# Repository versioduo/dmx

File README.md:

# dmx
🚥 MIDI to DMX Controller

## Configuration
Up to 16 DMX devices are mapped to 16 MIDI channels. The DMX
devices are configured by their base DMX address and the number
of DMX channels to control.

Default power-on values can be stored in the configuration. A MIDI
_System-Reset_ message will reset all devices and channels to their
configured power-on values.

For RGB devices, it is possible to use a separate set of more
intuitive CC values to control _Brightness_, _Colour_, _Saturation_;
the controller will calculate the RGB channel values accordingly.

## Controllers
MIDI Control Change (CC) values control the DMX channel values.

## Notes
The velocity value of a note overwrites the corresponding CC value
for the duration of the note; a MIDI _Note-Off_ will reset the DMX channel
value to the current CC value. A MIDI _All-Notes-Off_ message will restore
all devices and channels to the currently configured controller values.

During an active note, channel aftertouch will change the _Brightness_,
pitch bend will change the _Colour_.

There are two programs (MIDI _Program Change_) for notes. _Channels_
maps a range of consecutive notes to DMX channels.

_Brightness_ maps all received notes (the pitch is ignored) to control
only the brightness (or the first DMX channel of the device) of the DMX device.
If multiple notes are played at the same time, a MIDI _Note-Off_ will restore
the value of the earlier, still active note.

## Max For Live Device
An optional Ableton Max4Live [device](https://github.com/versioduo/max4live)
allows the the direct mapping from Live Automation to DMX values.

To avoid inconsistencies it will monitor the Live transport state, and update
all configured DMX channels of the current device every time _Play_ or
_Stop_ are triggered.

## Hardware

# Copying
Anyone can use this public domain work without having to seek authorisation, no one can ever own it.

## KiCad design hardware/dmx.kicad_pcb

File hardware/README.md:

# dmx-hardware

🚥 MIDI to DMX Bridge

## Board

## Schematic

[PDF](dmx.pdf)

## Bill Of Materials

[Interactive BOM](https://versioduo.com/view?url=https://raw.githubusercontent.com/versioduo/dmx/refs/heads/main/hardware/dmx-bom.html)

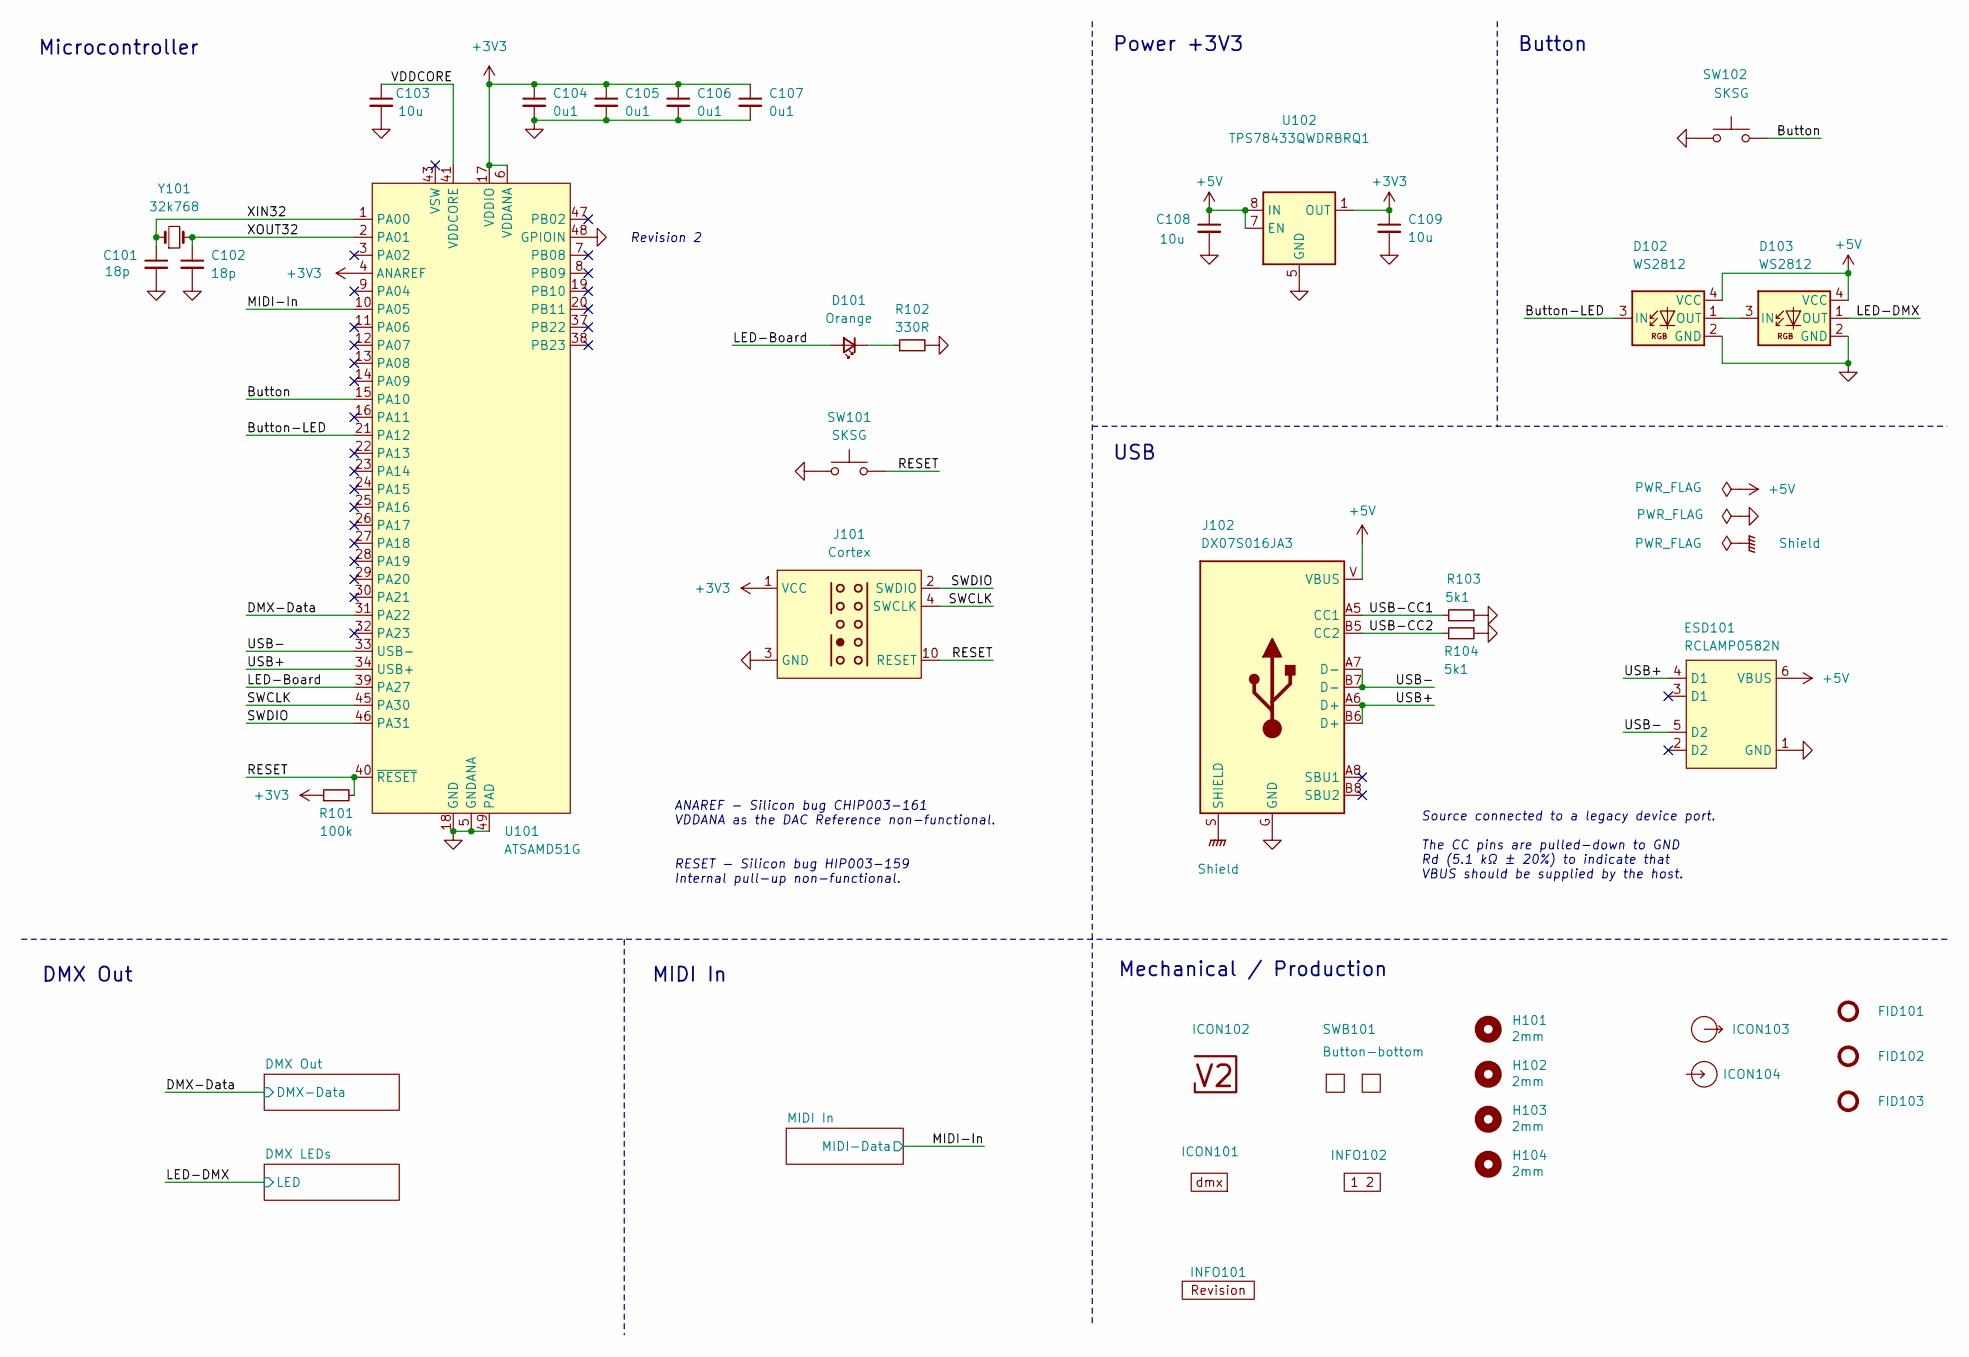
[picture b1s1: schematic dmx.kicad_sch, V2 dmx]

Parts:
C101, C102: 18p; C_1608; Rating 50V; Mouser 810-CGA3E2C0G1H180J
C103: 10u; C_1608; Rating 10V; Mouser 810-C1608X6S1A106M
C104, C105, C106, C107: 0u1; C_1608; Rating 50V; Mouser 810-CGA3E2X7R1H104MA
C108, C109: 10u; C_2012; Rating 25V; Mouser 810-C2012X5R1E106K
D101: Orange; LED_1608; Rating 605nm; Mouser 755-SML-D12D1WT86
D102, D103: WS2812; WS2812-2020; Rating 15mA; LCSC C965555
ESD101: RCLAMP0582N; SLP1210N6; Rating 20kV; Mouser 947-RCLAMP0582N.TCT
FID101, FID102, FID103: Fiducial_Paste; Fiducial_0.5mm_Mask1mm_Paste
H101, H102, H103, H104: 2mm; MountingHole_2mm
ICON101: Board_dmx; Board_dmx_Small
ICON102: V2-logo; Logo_Small
ICON103: Arrow_Out
ICON104: Arrow_In
INFO101: Revision
INFO102: Layer_Numbers-4
J101: Cortex
J102: DX07S016JA3; JAE_DX07S016JA3; Rating USB2.0; Mouser 656-DX07S016JA3R1500
R101: 100k; R_1608; Rating 100mW; Mouser 71-CRCW0603100KFKEAC
R102: 330R; R_1608; Rating 100mW; Mouser 71-CRCW0603330RFKEAC
R103, R104: 5k1; R_1608; Rating 100mW; Mouser 71-CRCW06035K10FKEAC
SW101, SW102: SKSG; Rating 1.6N; Mouser 688-SKSGACE010
SWB101: Button-bottom; PCB_Button-bottom
U101: ATSAMD51G; QFN-48-1EP_7x7mm_P0.5mm_EP5.45x5.45mm_ThermalVias; Rating Cortex-M4F; Mouser 556-ATSAMD51G19AMU
U102: TPS78433QWDRBRQ1; VSON-8-1_3x3mm_P0.65_EP1.65x2.4mm; Rating 300mA; Mouser 595-TPS78433QWDRBRQ1
Y101: 32k768; Crystal_SMD_3215-2Pin_3.2x1.5mm; Rating 10ppm; Mouser 815-ABS0716632.768KT

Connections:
+3V3: C104.1, C105.1, C106.1, C107.1, C109.1, J101.1 (VCC), R101.1, U101.4 (ANAREF), U101.6 (VDDANA), U101.17 (VDDIO), U101.36 (VDDIO), U101.44 (VDDIO), U102.1 (OUT); also elsewhere on the board
+5V: C108.1, D102.4 (VCC), D103.4 (VCC), ESD101.6 (VBUS), J102.V (VBUS), U102.7 (EN), U102.8 (IN); also elsewhere on the board
/Button: SW102.2, U101.15 (PA10)
/Button-LED: D102.3 (IN), U101.21 (PA12)
/DMX-Data: U101.31 (PA22); also elsewhere on the board
/LED-Board: D101.2 (A), U101.39 (PA27)
/LED-DMX: D103.1 (OUT); also elsewhere on the board
/MIDI-In: U101.10 (PA05); also elsewhere on the board
/RESET: J101.10 (RESET), R101.2, SW101.2, U101.40 (~RESET)
/SWCLK: J101.4 (SWCLK), U101.45 (PA30)
/SWDIO: J101.2 (SWDIO), U101.46 (PA31)
/Shield: J102.S (SHIELD)
/USB+: ESD101.4 (D1), J102.A6 (D+), J102.B6 (D+), U101.34 (USB+)
/USB-: ESD101.5 (D2), J102.A7 (D-), J102.B7 (D-), U101.33 (USB-)
/USB-CC1: J102.A5 (CC1), R103.1
/USB-CC2: J102.B5 (CC2), R104.1
/VDDCORE: C103.1, U101.41 (VDDCORE)
/XIN32: C101.1, U101.1 (PA00), Y101.1
/XOUT32: C102.1, U101.2 (PA01), Y101.2
GND: C101.2, C102.2, C103.2, C104.2, C105.2, C106.2, C107.2, C108.2, C109.2, D102.2 (GND), D103.2 (GND), ESD101.1 (GND), J101.3 (GND), J101.5 (GND), J102.G (GND), R102.2, R103.2, R104.2, SW101.1, SW102.1, U101.5 (GNDANA), U101.18 (GND), U101.35 (GND), U101.42 (GND), U101.48 (GPIOIN), U101.49 (PAD), U102.5 (GND), U102.9 (GND); also elsewhere on the board
unnamed: D101.1 (K), R102.1
unnamed: D102.1 (OUT), D103.3 (IN)

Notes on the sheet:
﻿ANAREF - Silicon bug CHIP003-161 VDDANA as the DAC Reference non-functional.
RESET - ﻿Silicon bug HIP003-159 Internal pull-up non-functional.
﻿Source connected to a legacy device port. The CC pins are pulled-down to GND Rd (5.1 kΩ ± 20%) to indicate that VBUS should be supplied by the host.
Button
Revision 2
Mechanical / Production
Power +3V3
Microcontroller
USB
DMX Out
MIDI In

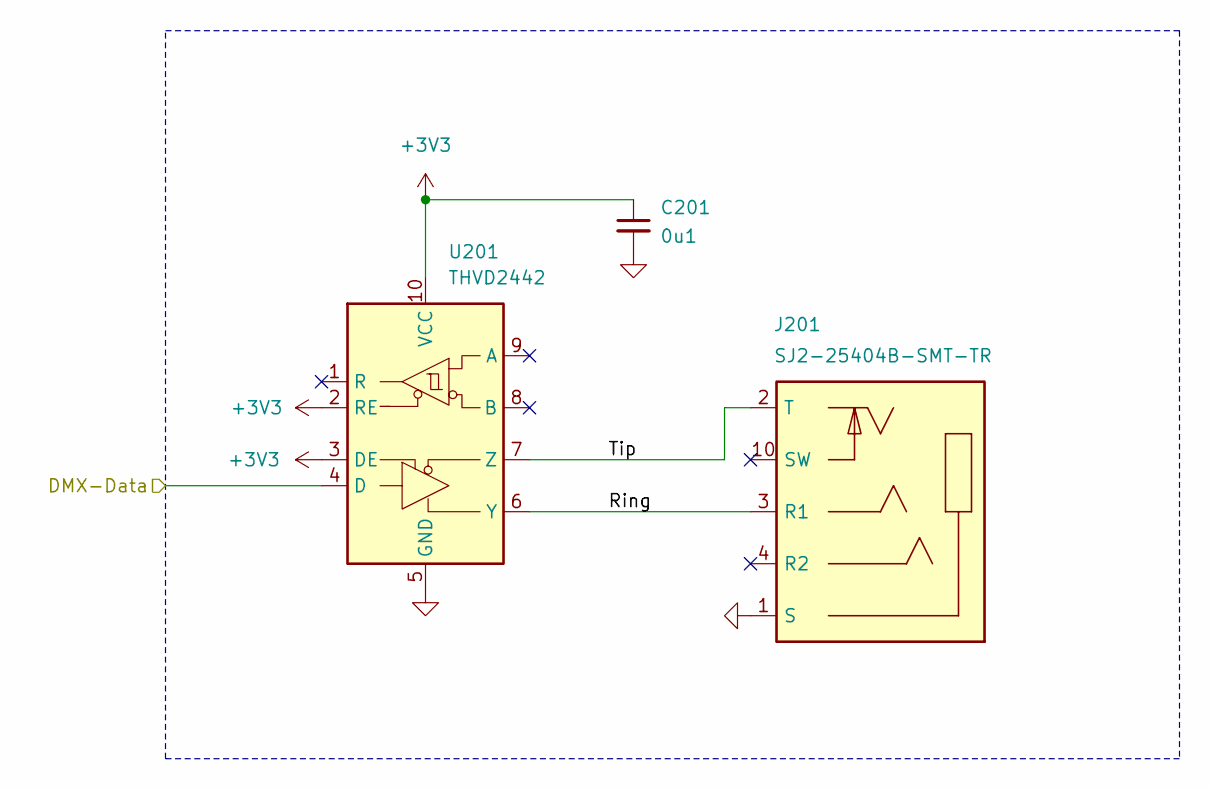
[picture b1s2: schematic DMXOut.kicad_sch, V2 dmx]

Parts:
C201: 0u1; C_1608; Rating 50V; Mouser 810-CGA3E2X7R1H104MA
J201: SJ2-25404B-SMT-TR; CUI_SJ2-25404B-SMT-TR; Rating 2.5mm; Mouser 490-SJ2-25404BSMT-TR
U201: THVD2442; VSON-10-4-1EP_3x3mm_P0.5mm_EP1.65x2.4mm_ThermalVias; Rating 20Mbps; Mouser 595-THVD2442DRCR

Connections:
+3V3: C201.1, U201.2 (RE), U201.3 (DE), U201.10 (VCC); also elsewhere on the board
/DMX Out/Ring: J201.3 (R1), U201.6 (Y)
/DMX Out/Tip: J201.2 (T), U201.7 (Z)
/DMX-Data: U201.4 (D); also elsewhere on the board
GND: C201.2, J201.1 (S), U201.5 (GND), U201.11 (GND); also elsewhere on the board

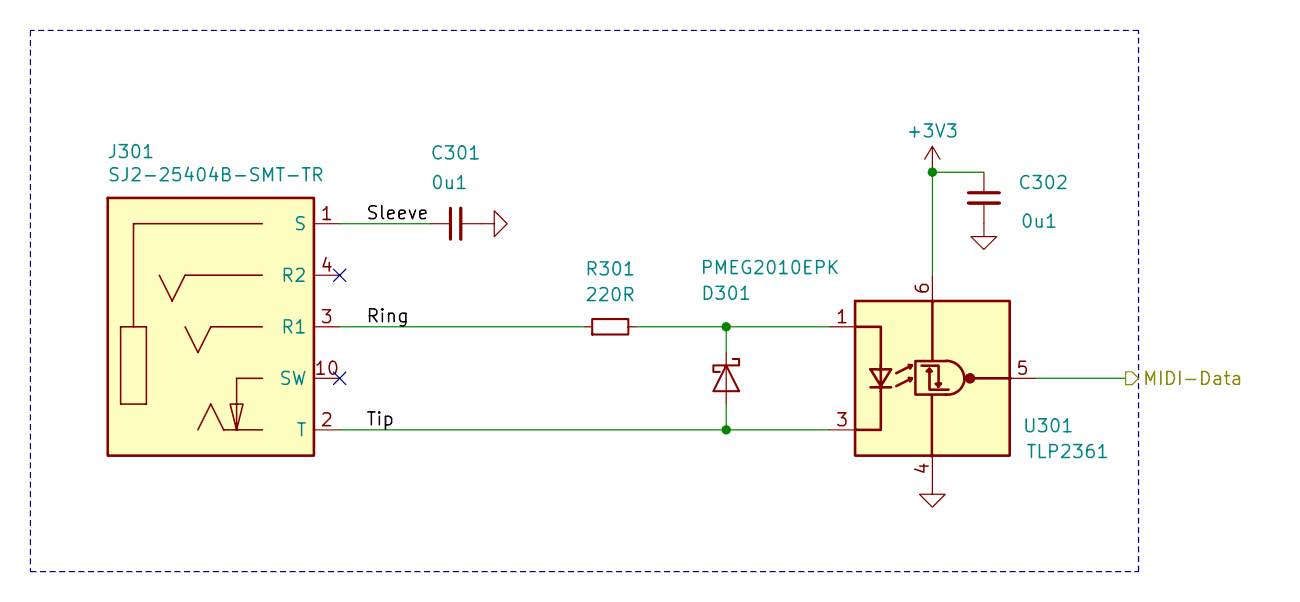
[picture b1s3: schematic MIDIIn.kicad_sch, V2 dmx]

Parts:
C301, C302: 0u1; C_1608; Rating 50V; Mouser 810-CGA3E2X7R1H104MA
D301: PMEG2010EPK; D_SOD-1608; Rating 20V; Mouser 771-PMEG2010EPK
J301: SJ2-25404B-SMT-TR; CUI_SJ2-25404B-SMT-TR; Rating 2.5mm; Mouser 490-SJ2-25404BSMT-TR
R301: 220R; R_1608; Rating 330mW; Mouser 71-CRCW0603220RFKEAH
U301: TLP2361; SO-5-6_4.55x3.7mm_P1.27mm; Rating 15Mbps; Mouser 757-TLP2361TPRE

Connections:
+3V3: C302.1, U301.6 (VDD); also elsewhere on the board
/MIDI In/Ring: J301.3 (R1), R301.1
/MIDI In/Sleeve: C301.1, J301.1 (S)
/MIDI In/Tip: D301.2 (A), J301.2 (T), U301.3 (K)
/MIDI-In: U301.5 (VO); also elsewhere on the board
GND: C301.2, C302.2, U301.4 (GND); also elsewhere on the board
unnamed: D301.1 (K), R301.2, U301.1 (A)

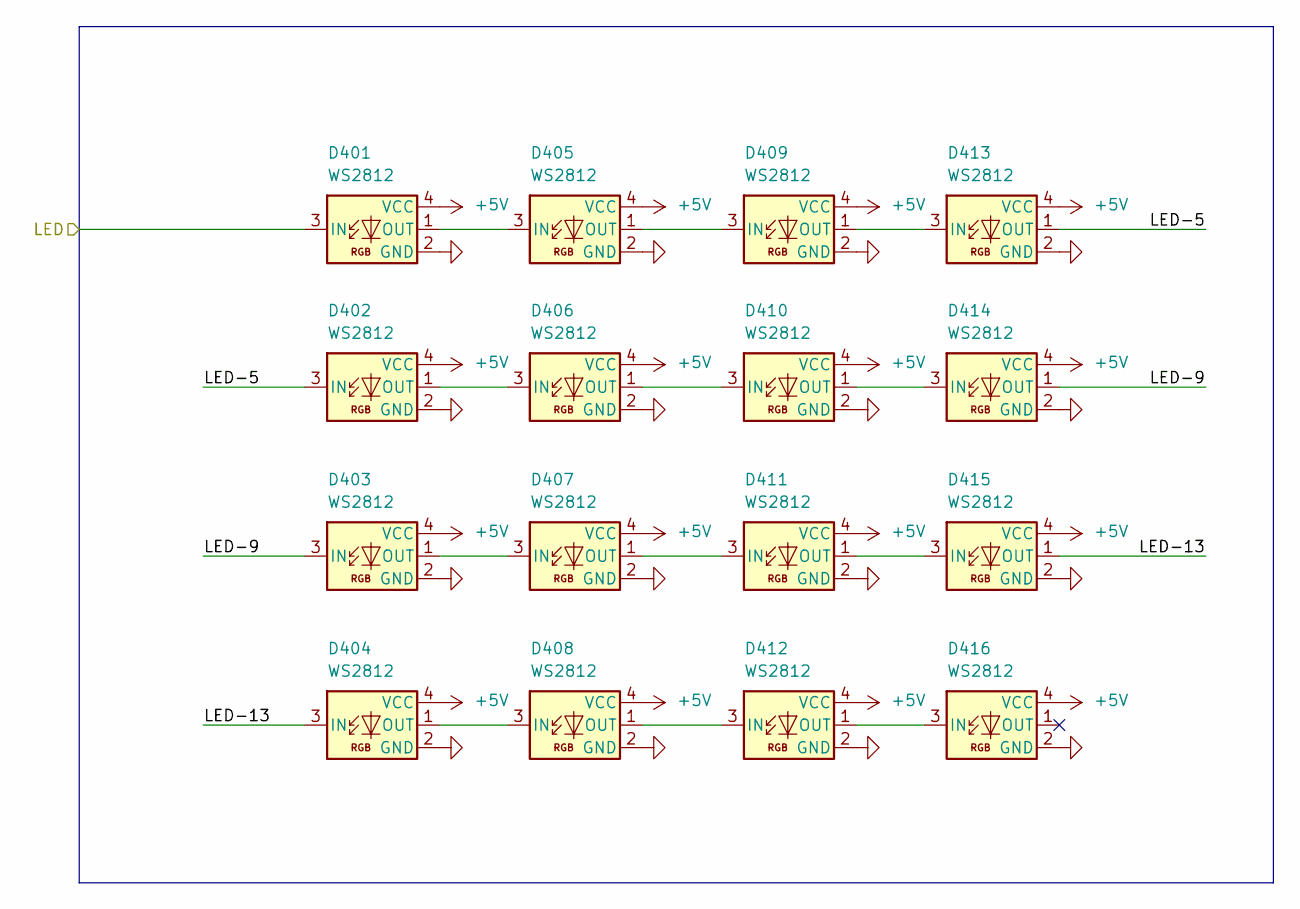
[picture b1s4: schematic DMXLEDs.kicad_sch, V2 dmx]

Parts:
D401, D402, D403, D404, D405, D406, D407, D408, D409, D410, D411, D412, D413, D414, D415, D416: WS2812; WS2812-2020; Rating 15mA; LCSC C965555

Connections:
+5V: D401.4 (VCC), D402.4 (VCC), D403.4 (VCC), D404.4 (VCC), D405.4 (VCC), D406.4 (VCC), D407.4 (VCC), D408.4 (VCC), D409.4 (VCC), D410.4 (VCC), D411.4 (VCC), D412.4 (VCC), D413.4 (VCC), D414.4 (VCC), D415.4 (VCC), D416.4 (VCC); also elsewhere on the board
/DMX LEDs/LED-5: D402.3 (IN), D413.1 (OUT)
/DMX LEDs/LED-9: D403.3 (IN), D414.1 (OUT)
/DMX LEDs/LED-13: D404.3 (IN), D415.1 (OUT)
/LED-DMX: D401.3 (IN); also elsewhere on the board
GND: D401.2 (GND), D402.2 (GND), D403.2 (GND), D404.2 (GND), D405.2 (GND), D406.2 (GND), D407.2 (GND), D408.2 (GND), D409.2 (GND), D410.2 (GND), D411.2 (GND), D412.2 (GND), D413.2 (GND), D414.2 (GND), D415.2 (GND), D416.2 (GND); also elsewhere on the board
unnamed: D401.1 (OUT), D405.3 (IN)
unnamed: D402.1 (OUT), D406.3 (IN)
unnamed: D403.1 (OUT), D407.3 (IN)
unnamed: D404.1 (OUT), D408.3 (IN)
unnamed: D405.1 (OUT), D409.3 (IN)
unnamed: D406.1 (OUT), D410.3 (IN)
unnamed: D407.1 (OUT), D411.3 (IN)
unnamed: D408.1 (OUT), D412.3 (IN)
unnamed: D409.1 (OUT), D413.3 (IN)
unnamed: D410.1 (OUT), D414.3 (IN)
unnamed: D411.1 (OUT), D415.3 (IN)
unnamed: D412.1 (OUT), D416.3 (IN)

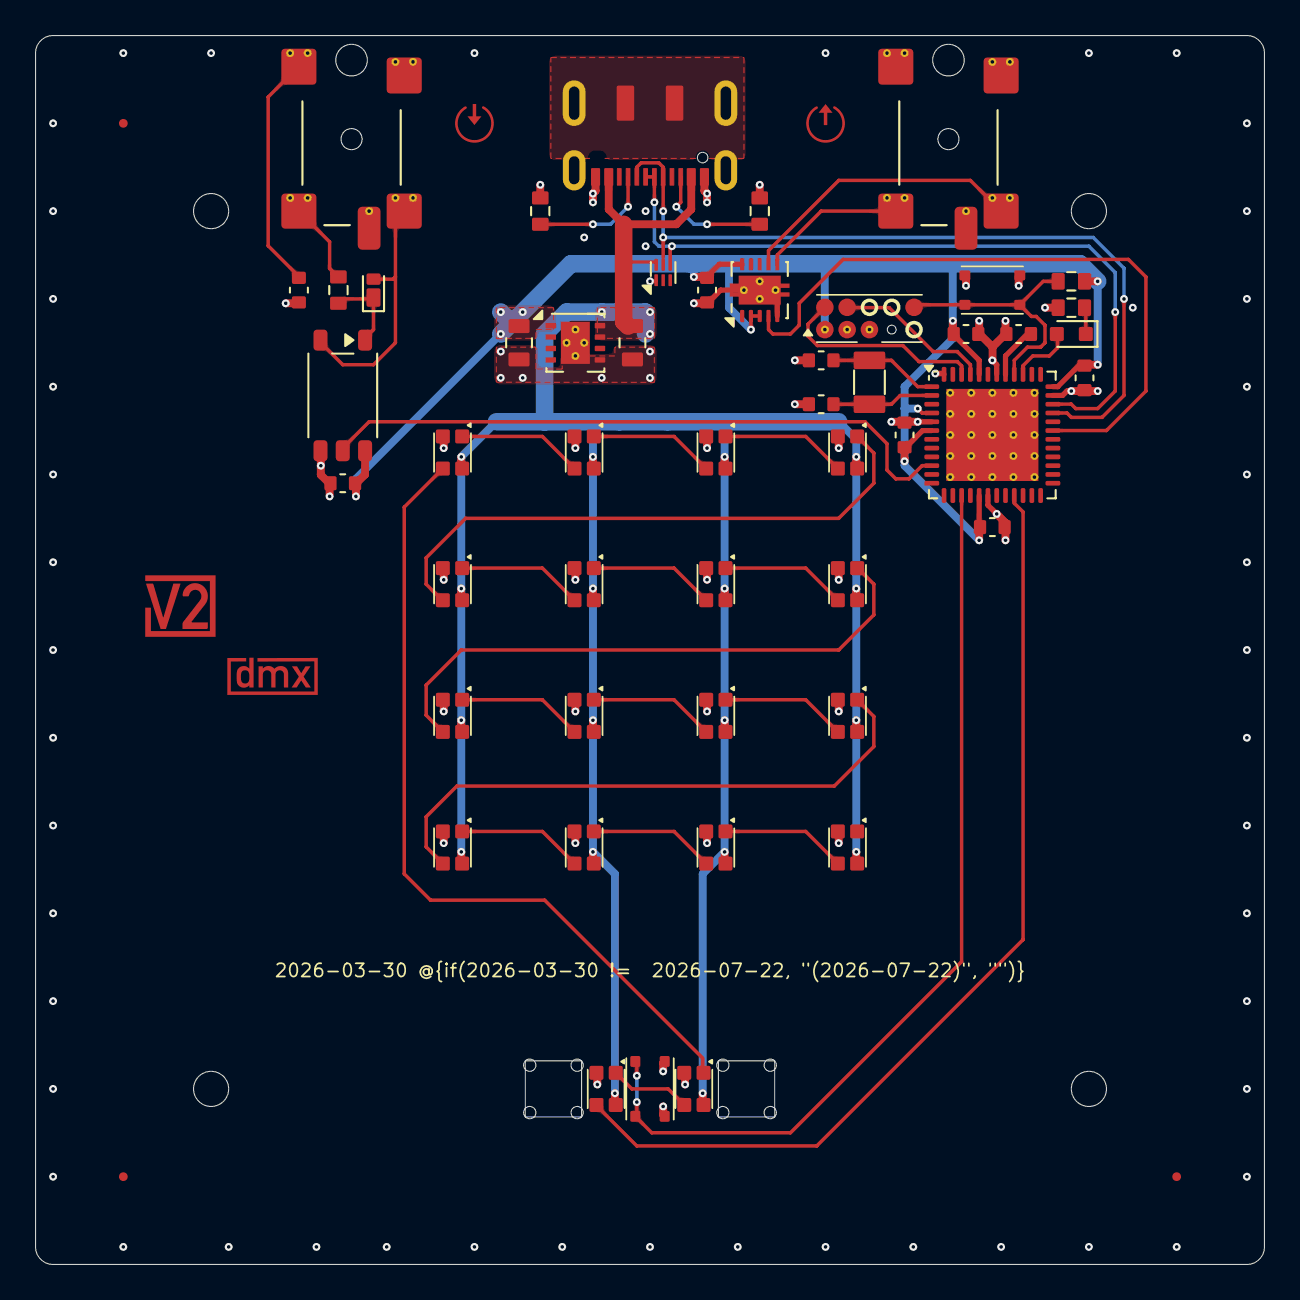
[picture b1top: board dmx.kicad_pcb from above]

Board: 4 copper layers, 70.0 x 70.0 mm, 63 parts (0 on the bottom side), 42 nets.

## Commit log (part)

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2020-10-13 Import
2020-10-13 Fixed typo on line 03
2023-05-15 Add Note Attack and Release fading
2023-05-21 Use 'Brightness' as the default program
2023-05-23 Support polyphonic (in addition to channel) aftertouch
2024-01-20 ArduinoJson 7
2025-11-05 Fix CC::BankSelectLSB without CC::BankSelect
2025-12-29 Colour
2026-01-06 Update symbols
2026-01-11 Refresh
2026-01-12 Update power symbols
2026-01-14 Update parts
2026-02-01 Update library
2026-02-02 Support channel LEDs
2026-02-10 Use date as revision
2026-02-13 Replace Order_Number
2026-02-25 Export stencil
2026-03-14 Update ESD suppressor
2026-03-30 Replace diode
2026-05-11 Good Bye Imperial
2026-06-23 Update V2MIDI API
